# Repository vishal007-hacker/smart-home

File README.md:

# Smart Home 4-Channel AC Relay Controller

**WisRight Technologies Private Limited**

ESP32-based smart home controller for switching 4 independent 230V AC loads, with per-channel current and voltage sensing, manual override buttons, status LEDs, and an I²C LCD display.

The project is a complete KiCad 9 design — schematic, PCB layout, BOM, custom symbol/footprint for the HLK-PM01 AC-DC module, custom DRC rules for mains clearance, and Python generator scripts that build everything from a single `bom.csv`.

## Features

- **4 independent AC channels**, each with its own L/N/PE input terminal, fuse, relay, and L/N output terminal
- **Mains isolation** — HLK-PM01 isolated AC-DC module (230VAC → 5VDC, 600mA, 2.1 kV isolation)
- **Per-channel current sensing** — ACS712-05B Hall-effect IC (±5A, isolated)
- **Per-channel voltage sensing** — external ZMPT101B modules via I²C ADS1115 (16-bit, 4 channels)
- **Manual override** — 4 tactile buttons for local on/off control per channel
- **Status indication** — 4 green LEDs (one per channel) + 1 red power LED
- **I²C LCD support** — 4-pin header for an external 16×2 PCF8574 backpack LCD
- **UART programming header** — standard 6-pin pinout for any USB-to-serial adapter
- **Custom DRC rules** — 4mm HV-to-LV clearance, 3mm HV-to-HV, 2mm HV trace minimum, edge clearance
- **HV/LV isolation slot** — physical cut in the PCB between mains and logic sections

## Hardware overview

| Section | Parts |
|---|---|
| AC inputs | 4× Phoenix MKDS-1.5 3-pos terminals (L, N, PE per channel) |
| Protection | 4× T4A 5×20mm fuses (one per channel) + 1× S07K275 MOV across L1/N1 |
| Power supply | HLK-PM01 (230VAC → 5VDC) + AMS1117-3.3 (5V → 3.3V LDO) |
| Switching | 4× SANYOU SRD-05VDC SPDT relays (10A) driven by ULN2003A Darlington array |
| MCU | ESP32-WROOM-32E module (WiFi + Bluetooth) |
| AC outputs | 4× Phoenix MKDS-1.5 2-pos terminals (L_switched, N_passthrough per channel) |
| Current sense | 4× ACS712-05B (SOIC-8, ±5A range, internal isolation) |
| Voltage sense | 4× external ZMPT101B modules via 1× ADS1115 (I²C ADC at 0x48) |
| User interface | 4× 6mm tactile buttons + 4× green status LEDs + 1× red power LED + 4-pin I²C LCD header |
| Programming | 6-pin UART header (GND, +3V3, TXD0, RXD0, EN, IO0) |

Full bill of materials in [`bom.csv`](bom.csv) — 43 grouped rows, 76 component instances.

## Detailed components list

### Active devices

| Ref | Qty | Part | Package | Description |
|---|---|---|---|---|
| **U1** | 1 | ESP32-WROOM-32E | Module 18×25.5mm | Espressif WiFi+BT MCU, 240MHz dual-core, 4MB flash, integrated PCB antenna |
| **U2** | 1 | ULN2003A | DIP-16 | Texas Instruments 7-channel Darlington array (500mA per channel, up to 50V), drives relay coils |
| **U3** | 1 | AMS1117-3.3 | SOT-223-3 | Advanced Monolithic Systems 3.3V LDO regulator, 1A capacity, drops 5V→3.3V for ESP32 |
| **PS1** | 1 | HLK-PM01 | THT 34.2×20.2mm | Hi-Link AC-DC isolated SMPS module, 230VAC→5VDC @ 600mA, 2.1 kV isolation, 3W |
| **U4-U7** | 4 | ACS712ELCTR-05B | SOIC-8 | Allegro Hall-effect current sensor, ±5A range, 185 mV/A sensitivity, 2.1 kVrms isolation between IP± and signal pins |
| **U8** | 1 | ADS1115IDGSR | TSSOP-10 | Texas Instruments 16-bit Σ-Δ ADC, 4 single-ended channels, I²C interface, 860 SPS, PGA ±0.256V to ±6.144V (default address 0x48 with ADDR=GND) |
| **K1-K4** | 4 | SRD-05VDC-SL-C | THT | Sanyou SPDT relay, 5V coil ~70mA, contacts rated 10A @ 250VAC / 30VDC |

### Discrete components

| Ref | Qty | Value | Package | Use |
|---|---|---|---|---|
| **R1-R4** | 4 | 1 kΩ | 0805 SMD | Status LED current limit (D1-D4) |
| **R9** | 1 | 1 kΩ | 0805 SMD | Power LED current limit (D5) |
| **R5-R8** | 4 | 10 kΩ | 0805 SMD | Manual button pull-ups to +3V3 (SW1-SW4) |
| **R11** | 1 | 10 kΩ | 0805 SMD | ESP32 EN pin pull-up to +3V3 |
| **R12** | 1 | 10 kΩ | 0805 SMD | ESP32 BOOT (GPIO0) pull-up to +3V3 |
| **R13** | 1 | 4.7 kΩ | 0805 SMD | I²C SDA pull-up to +3V3 |
| **R14** | 1 | 4.7 kΩ | 0805 SMD | I²C SCL pull-up to +3V3 |
| **R15-R18** | 4 | 10 kΩ | 0805 SMD | ACS712 output divider (top) — scales 0-5V to 0-3.21V for ESP32 ADC |
| **R19-R22** | 4 | 18 kΩ | 0805 SMD | ACS712 output divider (bottom) |
| **C1** | 1 | 100 µF / 16V | Radial THT 6.3mm | HLK-PM01 +5V output bulk capacitor (absorbs ESP32 WiFi transient bursts) |
| **C2** | 1 | 10 µF | 0805 SMD | AMS1117 input cap |
| **C3** | 1 | 22 µF | 0805 SMD | AMS1117 output cap (recommended ≥22µF tantalum/ceramic for AMS1117 stability) |
| **C4** | 1 | 10 µF | 0805 SMD | ESP32 +3V3 bulk |
| **C5** | 1 | 100 nF | 0805 SMD | ESP32 3V3 decoupling (place within 3mm of module pin 2) |
| **C6** | 1 | 1 µF | 0805 SMD | EN pin RC delay (forms ~10ms power-up delay with R11=10k) |
| **C7** | 1 | 100 nF | 0805 SMD | ULN2003A VCC decoupling |
| **C8-C11** | 4 | 100 nF | 0805 SMD | ACS712 VCC decoupling (one per ACS712) |
| **C16** | 1 | 100 nF | 0805 SMD | ADS1115 VDD decoupling |
| **D1-D4** | 4 | LED 3mm green | THT | Per-channel relay status indicator |
| **D5** | 1 | LED 3mm red | THT | Power-on indicator (always on while +5V present) |
| **F1-F4** | 4 | T4A 5×20 mm | THT Schurter 0031.8201 holder | Slow-blow mains fuse, one per AC input channel |
| **RV1** | 1 | S07K275 | Disc D9mm | EPCOS metal oxide varistor, 275 VAC clamping, surge protection across L1/N1 |

### Switches

| Ref | Qty | Type | Use |
|---|---|---|---|
| **SW1-SW4** | 4 | 6mm tactile THT | Manual override buttons (one per channel) — momentary press toggles the relay |
| **SW5** | 1 | 6mm tactile THT | BOOT button — hold during reset to enter ESP32 download mode |
| **SW6** | 1 | 6mm tactile THT | RESET button — pulls ESP32 EN low |

### Connectors

| Ref | Qty | Type | Use |
|---|---|---|---|
| **J1A, J1B, J1C, J1D** | 4 | Phoenix MKDS-1.5 3-pos screw terminal, 5.08mm pitch | AC input per channel: L (Live), N (Neutral), PE (Protective Earth) |
| **J2A, J2B, J2C, J2D** | 4 | Phoenix MKDS-1.5 2-pos screw terminal, 5.08mm pitch | AC switched output per channel: L_out, N_passthrough |
| **J3** | 1 | 1×6 pin header, 2.54mm pitch | UART programming: GND, +3V3, TXD0, RXD0, EN, IO0 |
| **J4** | 1 | 1×4 pin header, 2.54mm pitch | External 16×2 LCD via PCF8574 I²C backpack: GND, +5V, SDA, SCL |
| **J5, J6, J7, J8** | 4 | 1×3 pin header, 2.54mm pitch | External ZMPT101B voltage sensor per channel: GND, +3V3, VOUT |

### External modules (not on PCB — user-supplied)

| Module | Quantity | Purpose | Connection |
|---|---|---|---|
| 16×2 LCD with PCF8574 I²C backpack | 1 | Display | 4-wire to J4 (I²C address typically 0x27 or 0x3F) |
| ZMPT101B AC voltage transformer module | 4 | Per-channel voltage measurement | AC side wires to J1A/B/C/D L+N; DC side 3-wire to J5/J6/J7/J8 |
| USB-to-Serial adapter (CP2102, CH340, FT232) | 1 | Firmware upload | 4–6 wire to J3 (only used during flashing) |

### Custom library parts (included in repo)

| Part | Files | Source |
|---|---|---|
| **HLK-PM01 symbol** | [`lib/hlk_pm01.kicad_sym`](lib/hlk_pm01.kicad_sym) | Custom — drawn from datasheet |
| **HLK-PM01 footprint** | [`hlk_pm01.pretty/HLK-PM01.kicad_mod`](hlk_pm01.pretty/HLK-PM01.kicad_mod) | Custom — drawn from datasheet (34.2 × 20.2 × 15 mm body, 4-pin THT) |

All other symbols and footprints are pulled from KiCad 9's standard libraries.

## Board

| | |
|---|---|
| Size | 200 × 100 mm, 2-layer FR4, 1.6 mm |
| Net classes | Default (0.25mm), Power (0.5mm), AC_HV (2.5mm, 4mm clearance, red) |
| HV/LV separation | Physical slot at x=110..118 mm with 4 mm minimum clearance enforced via custom DRU |
| Mounting | 4× 3.2 mm holes at corners |

## ESP32 GPIO map

| GPIO | Function | Notes |
|---|---|---|
| GPIO16-19 | Relay control K1-K4 | Drives ULN2003A inputs 1-4 |
| GPIO21, 22, 23, 25 | Manual buttons SW1-SW4 | Active-low, 10k pull-up to 3V3 |
| GPIO26, 27, 32, 33 | Status LEDs D1-D4 | Active-high, 1k current limit |
| GPIO13 | I²C SDA | Shared bus: LCD (0x27) + ADS1115 (0x48) |
| GPIO14 | I²C SCL | Same shared bus |
| GPIO34, 35, 36, 39 | Current sense A0-A3 | ADC1 input from ACS712 voltage dividers |
| GPIO0 | BOOT button | SW5 + 10k pull-up |
| EN | RESET button | SW6 + 10k pull-up + 1uF RC delay |
| TXD0 (GPIO1) | UART TX | Programming header J3 pin 3 |
| RXD0 (GPIO3) | UART RX | Programming header J3 pin 4 |

ADS1115 reads voltage sensors V_SENSE_1..4 on its 4 single-ended inputs.

## Repository layout

```
.
├── README.md                       # This file
├── bom.csv                         # Bill of materials (source of truth)
├── smart_home.kicad_pro            # KiCad project file
├── smart_home.kicad_sch            # Schematic
├── smart_home.kicad_pcb            # PCB layout (routed)
├── smart_home.kicad_dru            # Custom DRC rules (HV clearance)
├── fp-lib-table / sym-lib-table    # Registers the local hlk_pm01 lib
├── lib/
│   └── hlk_pm01.kicad_sym          # Custom symbol for HLK-PM01
├── hlk_pm01.pretty/
│   └── HLK-PM01.kicad_mod          # Custom footprint for HLK-PM01
├── generate_sch.py                 # Builds smart_home.kicad_sch from bom.csv
├── generate_pcb.py                 # Builds initial smart_home.kicad_pcb
├── add_acs712.py                   # Adds current-sense ICs to PCB (preserves traces)
├── add_voltage_sense.py            # Adds ADS1115 + voltage-sense headers
└── fabrication/                    # Gerbers + drill + pick-and-place (regenerable)
```

## Building the design

### Regenerate schematic
```
"C:\Program Files\KiCad\9.0\bin\python.exe" generate_sch.py
```

### Regenerate PCB (initial placement only — overwrites routing)
```
"C:\Program Files\KiCad\9.0\bin\python.exe" generate_pcb.py
"C:\Program Files\KiCad\9.0\bin\python.exe" add_acs712.py
"C:\Program Files\KiCad\9.0\bin\python.exe" add_voltage_sense.py
```

### Run DRC / ERC
```
"C:\Program Files\KiCad\9.0\bin\kicad-cli.exe" sch erc smart_home.kicad_sch --output erc.json
"C:\Program Files\KiCad\9.0\bin\kicad-cli.exe" pcb drc smart_home.kicad_pcb --format json --output drc.json
```

### Export fabrication files
```
"C:\Program Files\KiCad\9.0\bin\kicad-cli.exe" pcb export gerbers smart_home.kicad_pcb -o fabrication/ --no-protel-ext
"C:\Program Files\KiCad\9.0\bin\kicad-cli.exe" pcb export drill smart_home.kicad_pcb -o fabrication/ --format excellon --excellon-units mm --generate-map --map-format gerberx2
"C:\Program Files\KiCad\9.0\bin\kicad-cli.exe" pcb export pos smart_home.kicad_pcb -o fabrication/smart_home-pos.csv --format csv --units mm
```

Zip everything in `fabrication/` and upload to [JLCPCB](https://jlcpcb.com), [PCBWay](https://pcbway.com), or [OSHPark](https://oshpark.com).

## Flashing firmware

Wire a USB-to-serial adapter (CP2102, CH340, FT232) to **J3**:

| J3 pin | Adapter |
|---|---|
| 1 — GND | GND |
| 2 — +3V3 | leave disconnected (board self-powered from mains via PS1) |
| 3 — TXD0 | RX |
| 4 — RXD0 | TX |
| 5 — EN | DTR (optional, for auto-reset) |
| 6 — IO0 | RTS (optional, for auto-boot) |

**Safety:** Disconnect mains before plugging in the USB adapter. Then power the board from mains for upload — PS1 supplies 5V/3.3V and is galvanically isolated from mains.

**Manual reset sequence:** hold SW5 (BOOT) → press+release SW6 (RESET) → release SW5 → click Upload in your IDE.

Compatible with Arduino-ESP32, ESP-IDF, MicroPython, PlatformIO.

## External wiring per channel

Each ZMPT101B voltage sensor module is wired externally:

```
AC side (off-PCB):
    J1A pin 1 (L1) ──┐
                     ├── ZMPT101B "AC IN"
    J1A pin 2 (N1) ──┘

DC side (3-wire to PCB):
    ZMPT101B GND ── J5 pin 1
    ZMPT101B VCC ── J5 pin 2 (+3V3)
    ZMPT101B OUT ── J5 pin 3 (→ ADS1115 A0)
```

Repeat for channels 2, 3, 4 via J6, J7, J8 (→ ADS1115 A1, A2, A3).

Calibrate the trimmer pot on each ZMPT101B so its output stays in 0–3.3V range.

## Safety

- The HV side (input terminals, fuses, relays, MOV, PS1 AC input) carries lethal mains voltage. **Always disconnect mains before working on the board.**
- The HV/LV isolation slot in the PCB and the 4 mm HV-to-LV clearance rule provide creepage isolation per IEC 60664-1 for pollution degree 2, working voltage 250V.
- Each input has its own T4A slow-blow fuse (F1–F4). Replace only with the same rating.
- HLK-PM01 provides galvanic isolation between mains and the 5V rail (2.1 kV rated).
- ACS712-05B provides 2.1 kVrms isolation between the load current path and the MCU side.
- Use a properly rated enclosure with strain-relief for mains wiring. Do not power up outside an enclosure.

This is a hobby project. The author assumes no liability for damage, injury, or fire resulting from its use. Build and operate at your own risk and in compliance with local electrical codes.

## License

MIT License.

Copyright © 2026 **WisRight Technologies Private Limited**.

Permission is hereby granted, free of charge, to any person obtaining a copy of this hardware design and associated documentation files, to use, copy, modify, merge, publish, distribute, sublicense, and/or sell copies of the design, subject to the standard MIT terms — provided as-is, without warranty of any kind, especially regarding electrical safety. See [LICENSE](LICENSE) for the full text.

## Maintainer

Designed and maintained by **WisRight Technologies Private Limited**.

For commercial inquiries, custom variants (different relay ratings, board sizes, sensor configurations, or firmware integration), please open an issue on this repository.

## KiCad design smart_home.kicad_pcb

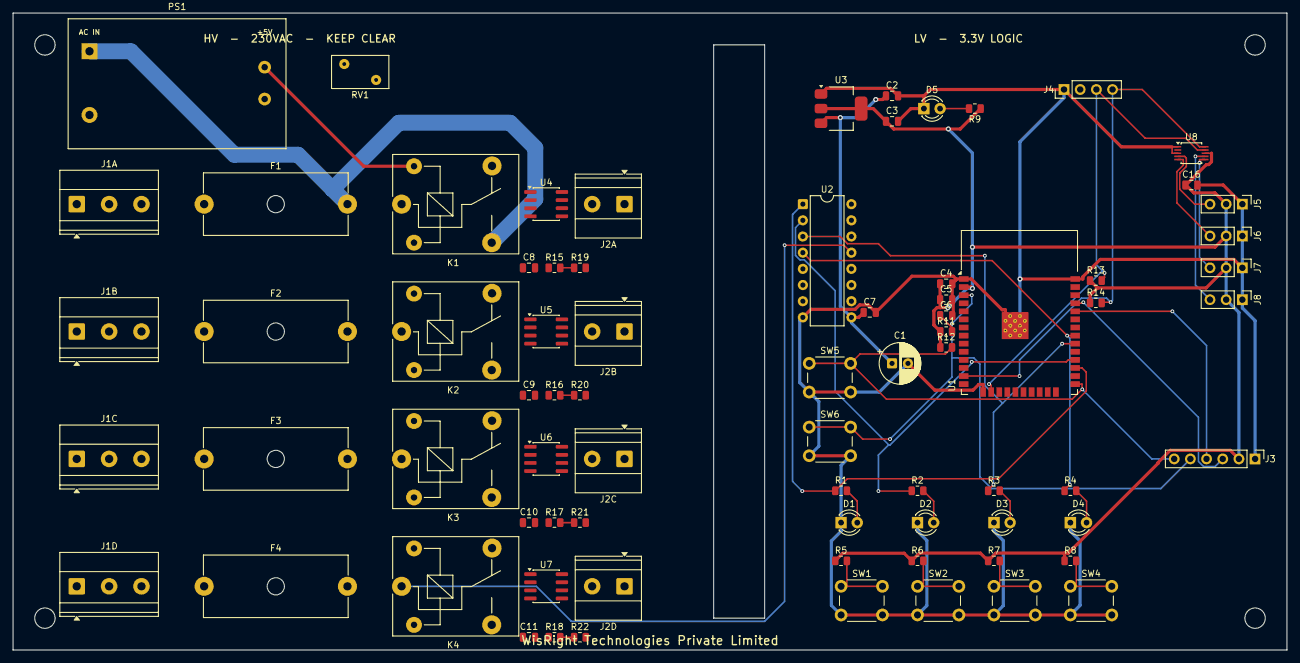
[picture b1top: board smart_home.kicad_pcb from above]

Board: 2 copper layers, 200.0 x 100.0 mm, 76 parts (0 on the bottom side), 59 nets.

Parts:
C1: 100uF/16V; CP_Radial_D6.3mm_P2.50mm
C2, C4: 10uF; C_0805_2012Metric
C3: 22uF; C_0805_2012Metric
C5, C7, C8, C9, C10, C11, C16: 100nF; C_0805_2012Metric
C6: 1uF; C_0805_2012Metric
D1, D2, D3, D4: LED_Green; LED_D3.0mm
D5: LED_Red; LED_D3.0mm
F1, F2, F3, F4: T4A; Fuseholder_Cylinder-5x20mm_Schurter_0031_8201_Horizontal_Op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
J1A: AC_IN_1; TerminalBlock_Phoenix_MKDS-1,5-3-5.08_1x03_P5.08mm_Horizont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
J1B: AC_IN_2; TerminalBlock_Phoenix_MKDS-1,5-3-5.08_1x03_P5.08mm_Horizont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
J1C: AC_IN_3; TerminalBlock_Phoenix_MKDS-1,5-3-5.08_1x03_P5.08mm_Horizont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
J1D: AC_IN_4; TerminalBlock_Phoenix_MKDS-1,5-3-5.08_1x03_P5.08mm_Horizont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
J2A: LOAD_1; TerminalBlock_Phoenix_MKDS-1,5-2-5.08_1x02_P5.08mm_Horizont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
J2B: LOAD_2; TerminalBlock_Phoenix_MKDS-1,5-2-5.08_1x02_P5.08mm_Horizont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
J2C: LOAD_3; TerminalBlock_Phoenix_MKDS-1,5-2-5.08_1x02_P5.08mm_Horizont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
J2D: LOAD_4; TerminalBlock_Phoenix_MKDS-1,5-2-5.08_1x02_P5.08mm_Horizont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
J3: PROG; PinHeader_1x06_P2.54mm_Vertical
J4: LCD I2C; PinHeader_1x04_P2.54mm_Vertical
J5: V_SENSE_1; PinHeader_1x03_P2.54mm_Vertical
J6: V_SENSE_2; PinHeader_1x03_P2.54mm_Vertical
J7: V_SENSE_3; PinHeader_1x03_P2.54mm_Vertical
J8: V_SENSE_4; PinHeader_1x03_P2.54mm_Vertical
K1, K2, K3, K4: SRD-05VDC-SL-C; Relay_SPDT_SANYOU_SRD_Series_Form_C
PS1: HLK-PM01
R1, R2, R3, R4, R9: 1k; R_0805_2012Metric
R5, R6, R7, R8, R11, R12, R15, R16, R17, R18: 10k; R_0805_2012Metric
R13, R14: 4.7k; R_0805_2012Metric
R19, R20, R21, R22: 18k; R_0805_2012Metric
RV1: S07K275; RV_Disc_D9mm_W5.2mm_P5mm
SW1, SW2, SW3, SW4, SW5, SW6: TACT_6mm; SW_PUSH_6mm
U1: ESP32-WROOM-32E; ESP32-WROOM-32
U2: ULN2003A; DIP-16_W7.62mm
U3: AMS1117-3.3; SOT-223-3_TabPin2
U4, U5, U6, U7: ACS712-05B; SOIC-8_3.9x4.9mm_P1.27mm
U8: ADS1115; TSSOP-10_3x3mm_P0.5mm

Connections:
+3V3: C3.1, C4.1, C5.1, C16.1, J3.2, J5.2, J6.2, J7.2, J8.2, R5.1, R6.1, R7.1, R8.1, R9.1, R11.1, R12.1, R13.1, R14.1, U1.2, U3.2, U8.8
+5V: C1.1, C2.1, C7.1, C8.1, C9.1, C10.1, C11.1, J4.2, K1.5, K2.5, K3.5, K4.5, PS1.3, U2.9, U3.3, U4.8, U5.8, U6.8, U7.8
BTN1: R5.2, SW1.1
BTN2: R6.2, SW2.1
BTN3: R7.2, SW3.1
BTN4: R8.2, SW4.1
COIL1: K1.1, U2.16
COIL2: K2.1, U2.15
COIL3: K3.1, U2.14
COIL4: K4.1, U2.13
EN: C6.1, J3.5, R11.2, SW6.1, U1.3
GND: C1.2, C2.2, C3.2, C4.2, C5.2, C6.2, C7.2, C8.2, C9.2, C10.2, C11.2, C16.2, D1.1, D2.1, D3.1, D4.1, D5.1, J3.1, J4.1, J5.1, J6.1, J7.1, J8.1, PS1.4, R19.2, R20.2, R21.2, R22.2, SW1.2, SW2.2, SW3.2, SW4.2, SW5.2, SW6.2, U1.1, U1.15, U1.38, U1.39, U2.8, U3.1, U4.5, U5.5, U6.5, U7.5, U8.1, U8.3
IO0: J3.6, R12.2, SW5.1, U1.25
IO16: R1.1, U1.27, U2.1
IO17: R2.1, U1.28, U2.2
IO18: R3.1, U1.30, U2.3
IO19: R4.1, U1.31, U2.4
I_SENSE_1: R15.2, R19.1
I_SENSE_2: R16.2, R20.1
I_SENSE_3: R17.2, R21.1
I_SENSE_4: R18.2, R22.1
L1: F1.2, K1.3, PS1.1, RV1.1
L1_RAW: F1.1, J1A.1
L2: F2.2, K2.3
L2_RAW: F2.1, J1B.1
L3: F3.2, K3.3
L3_RAW: F3.1, J1C.1
L4: F4.2, K4.3
L4_RAW: F4.1, J1D.1
LED1: D1.2, R1.2
LED2: D2.2, R2.2
LED3: D3.2, R3.2
LED4: D4.2, R4.2
LED_PWR: D5.2, R9.2
LOAD1: K1.2, U4.1, U4.2
LOAD1_OUT: J2A.1, U4.3, U4.4
LOAD2: K2.2, U5.1, U5.2
LOAD2_OUT: J2B.1, U5.3, U5.4
LOAD3: K3.2, U6.1, U6.2
LOAD3_OUT: J2C.1, U6.3, U6.4
LOAD4: K4.2, U7.1, U7.2
LOAD4_OUT: J2D.1, U7.3, U7.4
N1: J1A.2, J2A.2, PS1.2, RV1.2
N2: J1B.2, J2B.2
N3: J1C.2, J2C.2
N4: J1D.2, J2D.2
PE: J1A.3, J1B.3, J1C.3, J1D.3
RXD0: J3.4, U1.34
SCL_LCD: J4.4, R14.2, U1.13, U8.10
SDA_LCD: J4.3, R13.2, U1.16, U8.9
TXD0: J3.3, U1.35
VOUT_1: R15.1, U4.7
VOUT_2: R16.1, U5.7
VOUT_3: R17.1, U6.7
VOUT_4: R18.1, U7.7
V_SENSE_1: J5.3, U8.4
V_SENSE_2: J6.3, U8.5
V_SENSE_3: J7.3, U8.6
V_SENSE_4: J8.3, U8.7

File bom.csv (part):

Reference,Qty,Value,Description,KiCad Symbol,KiCad Footprint,Manufacturer Part No,Notes
U1,1,ESP32-WROOM-32E,WiFi+BT MCU module 240MHz dual-core 4MB flash,RF_Module:ESP32-WROOM-32E,RF_Module:ESP32-WROOM-32,ESP32-WROOM-32E-N4,Espressif. Keep antenna keep-out area clear of copper. 4MB flash is sufficient.
U2,1,ULN2003A,7-channel Darlington driver array for relay coils,Driver_Motor:ULN2003A,Package_DIP:DIP-16_W7.62mm,ULN2003AN,Texas Instruments / STMicroelectronics. DIP-16 for hand soldering; switch to SOIC-16W if reflow assembly.
U3,1,AMS1117-3.3,3.3V LDO linear regulator 1A,Regulator_Linear:AMS1117-3.3,Package_TO_SOT_SMD:SOT-223-3_TabPin2,AMS1117-3.3,Advanced Monolithic Systems. Needs >=22uF output cap for stability. SOT-223 tab is GND.
PS1,1,HLK-PM01,Isolated AC-DC SMPS 230VAC to 5VDC 600mA 2.1kV iso,hlk_pm01:HLK-PM01,hlk_pm01:HLK-PM01,HLK-PM01,Hi-Link. Custom KiCad symbol+footprint+3D model included in repo. 34.2x20.2x15mm THT.
K1-K4,4,SRD-05VDC-SL-C,SPDT relay 10A@250VAC 5V coil ~70mA,Relay:SANYOU_SRD_Form_C,Relay_THT:Relay_SPDT_SANYOU_SRD_Series_Form_C,SRD-05VDC-SL-C,Sanyou. One per channel. ULN2003 sink current is ~70mA at 5V coil supply.
U4-U7,4,ACS712-05B,Hall-effect AC current sensor +/-5A 185mV/A,Sensor_Current:ACS712xLCTR-05B,Package_SO:SOIC-8_3.9x4.9mm_P1.27mm,ACS712ELCTR-05B-T,Allegro Microsystems. One per channel. 2.1kVrms isolation IP+/- to signal pins. Load current MUST route through pins 1-4 (IP+) to pins 3-4 (IP-).
U8,1,ADS1115,4-channel 16-bit I2C ADC PGA 860SPS,Analog_ADC:ADS1115IDGS,Package_SO:TSSOP-10_3x3mm_P0.5mm,ADS1115IDGSR,Texas Instruments. I2C address 0x48 with ADDR=GND. Reads voltage from 4x external ZMPT101B modules via J5-J8. Shares I2C bus with LCD.
D1-D4,4,LED 3mm Green,Per-channel relay status indicator,Device:LED,LED_THT:LED_D3.0mm,LTL-4231N,Lite-On or any 3mm THT green LED. Vf ~2.2V at 5mA.
D5,1,LED 3mm Red,Power-on indicator (always on with +5V),Device:LED,LED_THT:LED_D3.0mm,LTL-4221N,Lite-On or any 3mm THT red LED. Vf ~2.0V at 5mA.
R1-R4,4,1k 0805,Status LED current limit for D1-D4,Device:R,Resistor_SMD:R_0805_2012Metric,RC0805FR-071KL,Yageo or any. Sets LED current ~3mA at 5V drive.
R9,1,1k 0805,Power LED current limit for D5,Device:R,Resistor_SMD:R_0805_2012Metric,RC0805FR-071KL,Same as R1-R4.
R5-R8,4,10k 0805,Manual button pull-up to +3V3 for SW1-SW4,Device:R,Resistor_SMD:R_0805_2012Metric,RC0805FR-0710KL,Yageo. Can be omitted if firmware enables ESP32 internal pull-ups.
R11,1,10k 0805,ESP32 EN pin pull-up to +3V3,Device:R,Resistor_SMD:R_0805_2012Metric,RC0805FR-0710KL,Required. Forms RC delay with C6 for clean power-up sequence.
R12,1,10k 0805,ESP32 BOOT (GPIO0) pull-up to +3V3,Device:R,Resistor_SMD:R_0805_2012Metric,RC0805FR-0710KL,Required. SW5 pulls IO0 low for download mode.
R13,1,4.7k 0805,I2C SDA pull-up to +3V3,Device:R,Resistor_SMD:R_0805_2012Metric,RC0805FR-074K7L,Required for I2C bus reliability with multiple devices (LCD + ADS1115).
R14,1,4.7k 0805,I2C SCL pull-up to +3V3,Device:R,Resistor_SMD:R_0805_2012Metric,RC0805FR-074K7L,Same as R13.
R15-R18,4,10k 0805,ACS712 ADC divider top (Vout -> ADC node),Device:R,Resistor_SMD:R_0805_2012Metric,RC0805FR-0710KL,One per ACS712. Divider ratio = 18/(10+18) = 0.643 scales 0-5V to 0-3.21V for ESP32 ADC.
R19-R22,4,18k 0805,ACS712 ADC divider bottom (ADC node -> GND),Device:R,Resistor_SMD:R_0805_2012Metric,RC0805FR-0718KL,One per ACS712. See R15-R18 note.
C1,1,100uF 16V,HLK-PM01 +5V output bulk capacitor,Device:C_Polarized,Capacitor_THT:CP_Radial_D6.3mm_P2.50mm,UVR1C101MED1TD,Nichicon or equivalent radial electrolytic. Absorbs ESP32 WiFi TX current bursts.
C2,1,10uF 0805,AMS1117 input bulk capacitor,Device:C,Capacitor_SMD:C_0805_2012Metric,CL21A106KOQNNNE,Samsung X5R or X7R MLCC.
C3,1,22uF 0805,AMS1117 output bulk capacitor,Device:C,Capacitor_SMD:C_0805_2012Metric,CL21A226MQQNNNE,Samsung X5R. AMS1117 requires >=22uF tantalum or ceramic for stability.
C4,1,10uF 0805,ESP32 +3V3 bulk capacitor,Device:C,Capacitor_SMD:C_0805_2012Metric,CL21A106KOQNNNE,X5R MLCC.
C5,1,100nF 0805,ESP32 +3V3 decoupling cap,Device:C,Capacitor_SMD:C_0805_2012Metric,CL21B104KBCNNNC,X7R MLCC. Place within 3mm of ESP32 module pin 2 (3V3).
C6,1,1uF 0805,EN pin RC delay capacitor,Device:C,Capacitor_SMD:C_0805_2012Metric,CL21B105KAFNNNE,X7R MLCC. With R11=10k forms 10ms RC delay on power-up.
C7,1,100nF 0805,ULN2003A VCC decoupling cap,Device:C,Capacitor_SMD:C_0805_2012Metric,CL21B104KBCNNNC,X7R MLCC.
C8-C11,4,100nF 0805,ACS712 VCC decoupling cap (one per IC),Device:C,Capacitor_SMD:C_0805_2012Metric,CL21B104KBCNNNC,X7R MLCC. Place within 3mm of ACS712 pin 8.
C16,1,100nF 0805,ADS1115 VDD decoupling cap,Device:C,Capacitor_SMD:C_0805_2012Metric,CL21B104KBCNNNC,X7R MLCC.
F1-F4,4,T4A 5x20mm,Slow-blow mains fuse (one per channel),Device:Fuse,Fuse:Fuseholder_Cylinder-5x20mm_Schurter_0031_8201_Horizontal_Open,0034.3122,Schurter 0034.3122 (T4AH 250V) + 0031.8201 holder. Rated 4A; matches relay 10A spec with safety margin.
RV1,1,S07K275,Metal oxide varistor 275VAC clamping (L1/N1),Device:Varistor,Varistor:RV_Disc_D9mm_W5.2mm_P5mm,S07K275,EPCOS / TDK. Surge protection across input 1 only (where logic supply taps). 270V continuous max.
SW1-SW4,4,6mm tactile THT,Manual override buttons (one per channel),Switch:SW_Push,Button_Switch_THT:SW_PUSH_6mm,TS-1102-G,Any 6mm tactile through-hole switch. Momentary action.
SW5,1,6mm tactile THT,BOOT button - hold during reset for download mode,Switch:SW_Push,Button_Switch_THT:SW_PUSH_6mm,TS-1102-G,Same as SW1-SW4. Pulls GPIO0 to GND.
SW6,1,6mm tactile THT,RESET button - pulls EN low,Switch:SW_Push,Button_Switch_THT:SW_PUSH_6mm,TS-1102-G,Same as SW1-SW4. Pulls EN to GND.
J1A,1,Screw terminal 3-pos,AC input ch1 - L1/N1/PE,Connector_Generic:Conn_01x03,"TerminalBlock_Phoenix:TerminalBlock_Phoenix_MKDS-1,5-3-5.08_1x03_P5.08mm_Horizontal",1715022,Phoenix Contact MKDS-1.5/3-5.08. Rated 16A 400VAC. Use 1.5mm^2 wire.
J1B,1,Screw terminal 3-pos,AC input ch2 - L2/N2/PE,Connector_Generic:Conn_01x03,"TerminalBlock_Phoenix:TerminalBlock_Phoenix_MKDS-1,5-3-5.08_1x03_P5.08mm_Horizontal",1715022,Same as J1A.
J1C,1,Screw terminal 3-pos,AC input ch3 - L3/N3/PE,Connector_Generic:Conn_01x03,"TerminalBlock_Phoenix:TerminalBlock_Phoenix_MKDS-1,5-3-5.08_1x03_P5.08mm_Horizontal",1715022,Same as J1A.
J1D,1,Screw terminal 3-pos,AC input ch4 - L4/N4/PE,Connector_Generic:Conn_01x03,"TerminalBlock_Phoenix:TerminalBlock_Phoenix_MKDS-1,5-3-5.08_1x03_P5.08mm_Horizontal",1715022,Same as J1A.
J2A,1,Screw terminal 2-pos,Load output ch1 - L1_OUT/N1,Connector_Generic:Conn_01x02,"TerminalBlock_Phoenix:TerminalBlock_Phoenix_MKDS-1,5-2-5.08_1x02_P5.08mm_Horizontal",1715019,Phoenix Contact MKDS-1.5/2-5.08. Rated 16A 400VAC.
J2B,1,Screw terminal 2-pos,Load output ch2 - L2_OUT/N2,Connector_Generic:Conn_01x02,"TerminalBlock_Phoenix:TerminalBlock_Phoenix_MKDS-1,5-2-5.08_1x02_P5.08mm_Horizontal",1715019,Same as J2A.
J2C,1,Screw terminal 2-pos,Load output ch3 - L3_OUT/N3,Connector_Generic:Conn_01x02,"TerminalBlock_Phoenix:TerminalBlock_Phoenix_MKDS-1,5-2-5.08_1x02_P5.08mm_Horizontal",1715019,Same as J2A.
J2D,1,Screw terminal 2-pos,Load output ch4 - L4_OUT/N4,Connector_Generic:Conn_01x02,"TerminalBlock_Phoenix:TerminalBlock_Phoenix_MKDS-1,5-2-5.08_1x02_P5.08mm_Horizontal",1715019,Same as J2A.
J3,1,Pin header 1x06 2.54mm,UART programming header,Connector_Generic:Conn_01x06,Connector_PinHeader_2.54mm:PinHeader_1x06_P2.54mm_Vertical,M20-9990645,Harwin or any 6-pin 0.1in vertical header. Pinout: GND / +3V3 / TXD0 / RXD0 / EN / IO0.
J4,1,Pin header 1x04 2.54mm,External 16x2 LCD I2C connector,Connector_Generic:Conn_01x04,Connector_PinHeader_2.54mm:PinHeader_1x04_P2.54mm_Vertical,M20-9990445,4-pin 0.1in vertical header. Pinout: GND / +5V / SDA / SCL. Connects to a PCF8574-backpack LCD (I2C 0x27 or 0x3F).
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
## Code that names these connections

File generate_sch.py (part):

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    #   pin 6 = IO34       / ADC1_CH6
    #   pin 7 = IO35       / ADC1_CH7
    # Assignment per spec:
    #   I_SENSE_1 -> IO34 (pin 6), I_SENSE_2 -> IO35 (pin 7),
    #   I_SENSE_3 -> IO36 (pin 4), I_SENSE_4 -> IO39 (pin 5).
    # U1 is at (295, 120) on the schematic; module pin spacing is 1.27mm.
    # Pin 1 is top-left; pins 1..19 down the left side, then 20..38 up the
    # right side. In the .kicad_sym placement these come out at offsets
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    # Since the actual symbol layout depends on the lib, we place the labels
    # near U1 (center 295,120) using the same rough scheme used for IO16-19.
    for net, x, y in [
        ("I_SENSE_1", 283, 130),   # IO34 (pin 6)
        ("I_SENSE_2", 283, 132),   # IO35 (pin 7)
        ("I_SENSE_3", 283, 134),   # IO36 (pin 4)
        ("I_SENSE_4", 283, 136),   # IO39 (pin 5)
    ]:
        labels.append(emit_label(net, x, y))

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        ("V_SENSE_4", 233, 55),
        ("+3V3",      245, 73),     # U8 pin 8 VDD
        ("GND",       245, 50),     # U8 pin 3 GND
        ("SCL_LCD",   256, 60),     # U8 pin 10 SCL
        ("SDA_LCD",   256, 58),     # U8 pin 9 SDA
        ("GND",       256, 55),     # U8 pin 1 ADDR -> GND (sets addr 0x48)
        # ALERT/RDY pin 2 intentionally left floating (no label)
        # C16 100nF decoupling near U8 VDD/GND
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        # slightly to the left of each header's pin positions.
        ("GND",       390, 130),    # J5 pin 1
        ("+3V3",      390, 133),    # J5 pin 2
        ("V_SENSE_1", 390, 135),    # J5 pin 3
        ("GND",       390, 150),    # J6 pin 1
        ("+3V3",      390, 153),    # J6 pin 2
        ("V_SENSE_2", 390, 155),    # J6 pin 3
        ("GND",       390, 170),    # J7 pin 1
        ("+3V3",      390, 173),    # J7 pin 2
        ("V_SENSE_3", 390, 175),    # J7 pin 3
        ("GND",       390, 190),    # J8 pin 1
        ("+3V3",      390, 193),    # J8 pin 2
        ("V_SENSE_4", 390, 195),    # J8 pin 3
    ]:
        labels.append(emit_label(net, x, y))

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        ("SDA_LCD", 367, 50), ("+3V3", 373, 50),
        # Pull-up resistor R14 (SCL <-> +3V3)
        ("SCL_LCD", 367, 60), ("+3V3", 373, 60),
        # J4 header pin 3 = SDA_LCD, pin 4 = SCL_LCD
        # J4 placed at (395, 60); pin labels distributed vertically
        ("GND", 397, 58),       # J4 pin 1
        ("+5V", 397, 60),       # J4 pin 2
        ("SDA_LCD", 397, 62),   # J4 pin 3
        ("SCL_LCD", 397, 64),   # J4 pin 4
    ]:
        labels.append(emit_label(net, x, y))

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
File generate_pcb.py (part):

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
    # ---- LCD I2C external connector + I2C pull-ups ----
    # J4: 4-pin vertical header for an external 16x2 LCD via PCF8574 I2C
    # backpack. Pinout: 1=GND, 2=+5V, 3=SDA_LCD, 4=SCL_LCD.
    # PinHeader_1x04 footprint pads (rot=0): pad1 at (0,0); pads 2..4 stack
    # in +Y at (0,2.54),(0,5.08),(0,7.62). Courtyard ~(-1.8,-1.8)..(1.8,9.42).
    # Use rot=90 so pads stack in +X instead -> easier top-edge cable access
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#   9     = COMMON (relay coil supply diode anode)
#   10..16 = outputs OUT7..OUT1 (16 mirrors 1, 15 mirrors 2, etc.)
# Use IN1..IN4 (pins 1..4) driven by ESP32 IO16..IO19, OUT1..OUT4
# (pins 16,15,14,13) drive coil low side (COIL1..COIL4). Pin 9 to +5V,
# pin 8 to GND.
#
# AMS1117-3.3 (SOT-223-3_TabPin2): pin 1=ADJ/GND, pin 2=OUT (tab), pin 3=IN
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}

# J4: LCD I2C external connector (4-pin).
# Pinout: 1=GND, 2=+5V (PCF8574 backpack + HD44780 contrast), 3=SDA_LCD, 4=SCL_LCD.
PAD_NETS["J4"] = {
    "1": "GND",
    "2": "+5V",
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
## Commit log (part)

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2026-06-26 Complete 4-channel smart home AC relay PCB design
    Full KiCad 9 design for a 230V AC 4-channel smart home relay controller:
    - ESP32-WROOM-32E + ULN2003A + 4x SANYOU SRD relays
    - 4 isolated AC inputs (own L/N/PE + fuse per channel)
    - 4 AC outputs (L_switched + N_passthrough per channel)
    - HLK-PM01 isolated AC-DC + AMS1117-3.3 LDO for logic
    - Per-channel current sense (4x ACS712-05B + ADC dividers)
2026-06-26 Add full component details to README and company name to PCB
    - Update company in title block: Wisright -> WisRight Technologies Private Limited
    (smart_home.kicad_sch, smart_home.kicad_pcb, generate_sch.py)
    - Add silkscreen on PCB:
    * Front silk (bottom center): "WisRight Technologies Private Limited" (bold 1.4mm)
    * Back silk (top, mirrored): "Smart Home 4-Channel AC Relay Controller - Rev 0.1"
    * Back silk (bottom, mirrored): "(c) 2026 WisRight Technologies Pvt Ltd"
2026-06-26 Add 3D model for HLK-PM01 (was missing in 3D viewer)
    Create hlk_pm01.pretty/HLK-PM01.wrl — VRML 2.0 model representing
    the 34.2 x 20.2 x 15 mm black plastic enclosure with a lighter top label area.
    Reference the model from both the library footprint (HLK-PM01.kicad_mod)
    and the PCB's embedded instance (smart_home.kicad_pcb PS1 footprint).
    The 3D viewer in KiCad PCB editor now shows the HLK-PM01 module body
    sitting on the board instead of just the silkscreen outline.
2026-06-26 Include HLK-PM01.wrl in repo (gitignore fix)
    The previous commit added hlk_pm01.pretty/HLK-PM01.wrl on disk but the
    *.wrl gitignore pattern silently dropped it from version control.
    Restrict the WRL ignore so .wrl files inside *.pretty/ footprint
    directories are tracked (they are part of the design, not output).
2026-06-26 Fix HLK-PM01 3D model scale (was rendered ~3x oversize)
    KiCad VRML legacy convention treats 1 WRL unit = 0.1 inch = 2.54 mm.
    Since the model is authored in mm, set scale to 1/2.54 = 0.3937 in both
    the library footprint and the PCB instance so the body renders at its
    real 34.2 x 20.2 x 15 mm dimensions.
2026-06-26 Expand BOM with manufacturer parts, sourcing notes, external modules
    bom.csv:
    - Add manufacturer names (Espressif, TI, Allegro, Phoenix Contact, etc.)
    - Add specific MPNs for sourcing (Yageo / Samsung MLCC / Schurter fuse holder)
    - Properly quote J1A-J1D and J2A-J2D footprint fields (the unquoted commas
    in MKDS-1,5 part names were a CSV parsing hazard)
    - More descriptive Notes per part (placement guidance, alternatives, ratings)
2026-06-26 Run Freerouting autoroute on updated PCB (post ACS712+ADS1115)
    Process:
    1. Pcbnew Python API: rip up all 426 stale tracks/42 vias from prior pass
    (they predated the ACS712 net-topology change and were inconsistent)
    2. Export fresh Specctra DSN (smart_home.dsn)
    3. Freerouting 1.9.0 batch autoroute, 50 passes, 4 threads
    4. Import SES back via pcbnew.ImportSpecctraSES
